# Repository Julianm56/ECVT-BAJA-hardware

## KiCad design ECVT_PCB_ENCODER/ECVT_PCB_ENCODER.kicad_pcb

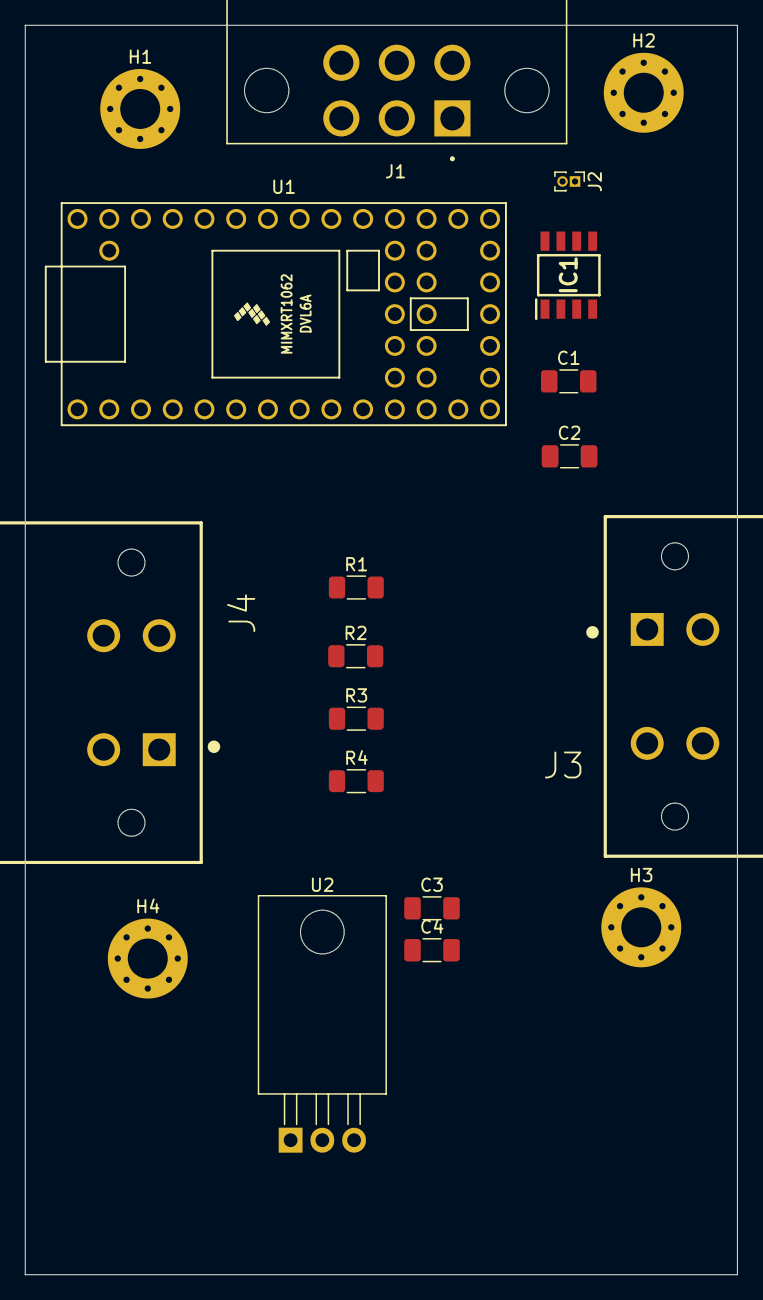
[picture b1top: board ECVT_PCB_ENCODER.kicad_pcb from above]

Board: 2 copper layers, 57.0 x 100.0 mm, 19 parts (0 on the bottom side), 13 nets, no tracks yet.

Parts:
C1: 100nF; C_1206_3216Metric_Pad1.33x1.80mm_HandSolder
C2: 47uF; C_1206_3216Metric_Pad1.33x1.80mm_HandSolder
C3: 0.33uF; C_1206_3216Metric_Pad1.33x1.80mm_HandSolder
C4: 0.1uF; C_1206_3216Metric_Pad1.33x1.80mm_HandSolder
H1, H2, H3, H4: GND; MountingHole_3.2mm_M3_Pad_Via
IC1: TJA1051T; SOIC127P600X175-8N
J1: DTF13-6P; TE_DTF13-6P
J2: 120R; PinHeader_1x02_P1.00mm_Vertical
J3, J4: DTF13-4P; TE_DTF13-4P
R1, R3, R4: 1K; R_1206_3216Metric_Pad1.30x1.75mm_HandSolder
R2: 1k; R_1206_3216Metric_Pad1.30x1.75mm_HandSolder
U1: Teensy4.0; Teensy40
U2: L7805; TO-220-3_Horizontal_TabDown

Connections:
+3.3V: R1.1, R2.2, R3.1, R4.2, U1.16 (3V3)
/+5V: J3.4, J4.4
/CAN_HIGH: IC1.7 (CANH), J1.4, J1.5, J2.2
/CAN_LOW: IC1.6 (CANL), J1.2, J1.3, J2.1
/CAN_RX: IC1.4 (RXD), U1.30 (23_A9_CRX1_MCLK1)
/CAN_TX: IC1.1 (TXD), U1.29 (22_A8_CTX1)
/REG_VIN: C1.1, C2.1, C4.1, IC1.3 (VCC), U1.33 (VIN), U2.3 (OUT)
/SigA_IS: J3.2, R2.1, U1.5 (3_LRCLK2)
/SigA_OS: J4.2, R4.1, U1.7 (5_IN2)
/SigB_IS: J3.3, R1.2, U1.4 (2_OUT2)
/SigB_OS: J4.3, R3.2, U1.6 (4_BCLK2)
/VIN: C3.1, J1.6, U2.1 (IN)
GND: C1.2, C2.2, C3.2, C4.2, IC1.2 (GND), IC1.8 (S), J1.1, J3.1, J4.1, U1.1 (GND), U1.17 (GND), U1.32 (GND), U2.2 (GND)
